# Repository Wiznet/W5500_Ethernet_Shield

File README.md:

# W5500 Ethernet Shield

## Overview

- Arduino Pin-compatible
- ARM mbed compatible operation
- Ethernet (W5500 Hardwired TCP/IP chip)

W5500 Ethernet shield is designed using the WIZnet W5500 chip. Please click the link for the further information about W5500. It supports both 3.3V & 5V. This Ethernet Shield is compatible with Arduino and ARM mbed Platform.

### Available Board List

- ARM mbed Board
	- ARM mbed Platform : ARM mbed platform Site
	- FRDM-KL25Z : Freescale
	- NXP LPC800-MAX : NXP
- Arduino Board
	- Arduino board (e.g. the Uno, Mega, Due)
	- Arduino Leonardo
- Arduino-compatible Board
	- Seeeduino v3.0 : Based on Arduino Duemilanove

## Getting Started

- [Getting Started fot Arduino](https://wizwiki.net/wiki/doku.php?id=osh:w5500_ethernet_shield_getting_started#step_2installing_the_ethernet2_library)
- [Ethernet/Ethernet2 library Reference](https://www.arduino.cc/en/Reference/Ethernet)

## Feature

- Ethernet controller W5500 of WIZnet
- SPI interface
- Internal 32Kbytes Tx/Rx buffer
- 10/100 Ethernet PHY embedded
- Hardwired TCP/IP Protocols : TCP, UDP, ICMP, IPv4, ARP, IGMP, PPPoE
- User Selectable GPIO pin
- Support SD-card slot for storage
- Support 3.3V and 5V

## Hardware Configuration
- RJ-45 with Transformer : Ethernet Port
- W5500 : a Hardwired TCP/IP Ethernet Controller
- RESET : Reset Ethernet shield and Arduino when pressed
- SD-Slot : support Micro SD card in FAT16 or FAT32 ; (Please read 'Caution' below)

## Pins usage on Arduino & ARM mbed

W5500 Ethernet shield has several configurable GPIOs

- When you operate it with other modules, you may need to change 'Chip Select' pin to a different one.
- W5500 INTn pin is linked to D2 (2,3 Short). So, if you need INTn pin. You soldering to 0R Resistor to Dx pin

**Caution)** When the user uses 5V Platform, we cannot confirm a stable operation of SD-CARD. Therefore, though 5V Platform is safe to use after going through enough tests, it is highly recommended to mount buffer & 100nF Capacitor for a secure operation.

## SPI Operation & Timing Diagram

There is a W5500 inside W5500 Ethernet shield. Therefore SPI operation & Timing Diagram of Ethernet shield follows one of W5500. For more information about W5500 chip please also refer to the chip's datasheet:

- [W5500 Wiki](https://wizwiki.net/wiki/doku.php?id=products:w5500:start)

## Dimension

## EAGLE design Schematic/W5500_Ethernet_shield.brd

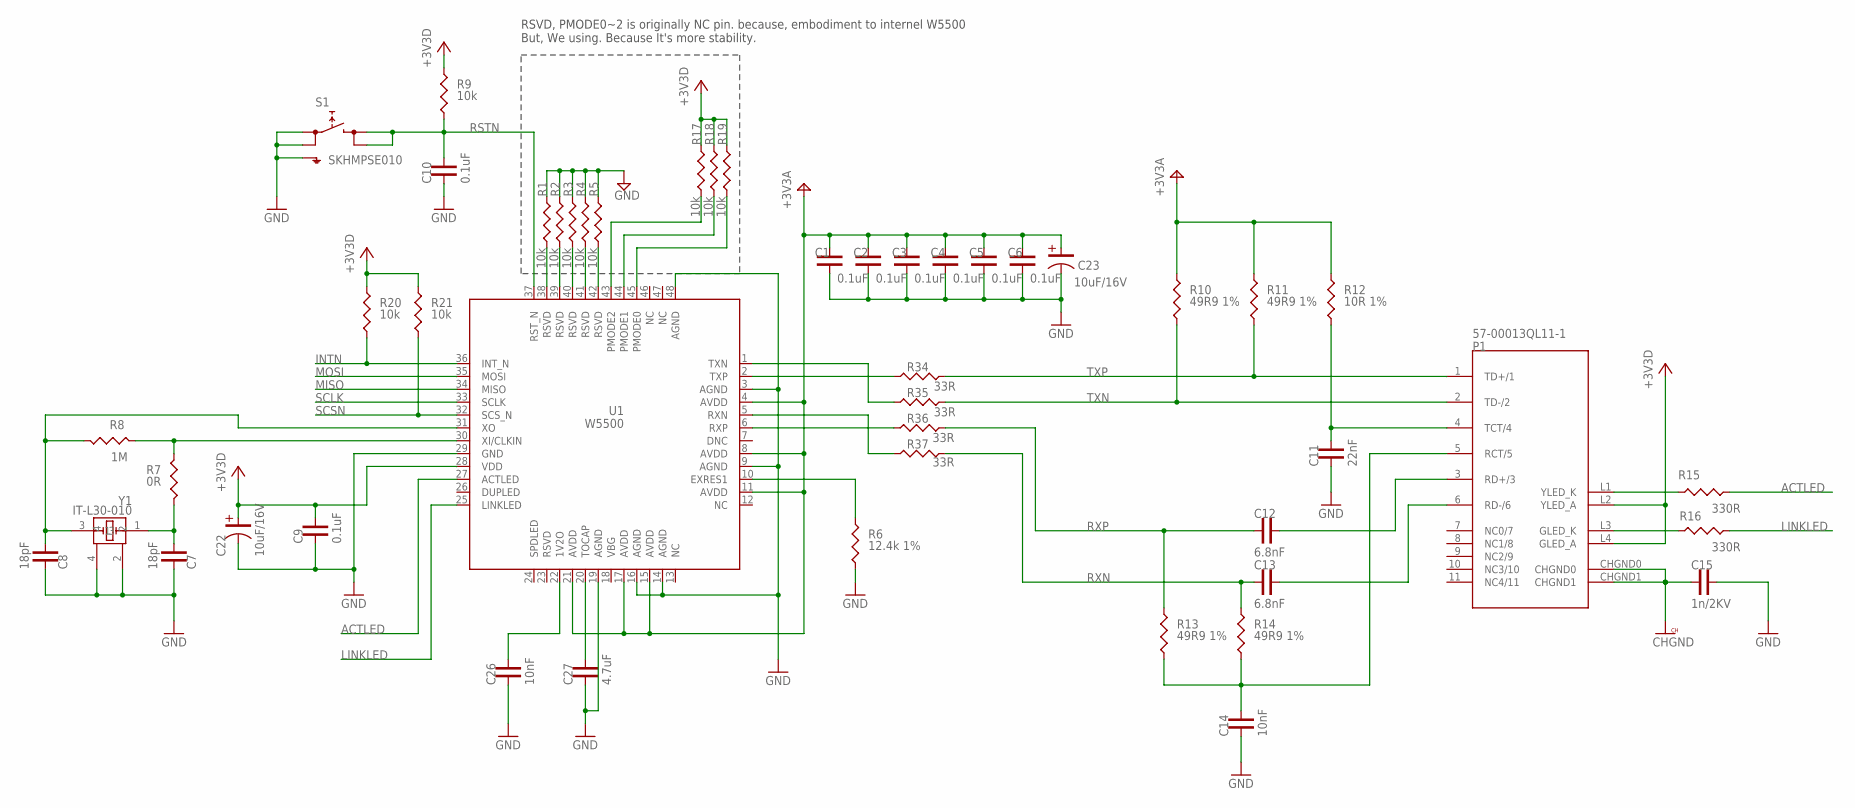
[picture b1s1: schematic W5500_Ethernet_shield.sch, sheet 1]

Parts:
C1, C2, C3, C4, C5, C6, C9, C10: 0.1uF; C-1608
C7, C8: 18pF; C-1608
C11: 22nF; C-1608
C12, C13: 6.8nF; C-1608
C14, C26: 10nF; C-1608
C15: 1n/2KV; C-1808
C22, C23: 10uF/16V; C-3216(TANTAL)
C27: 4.7uF; C-2012
P1: 57-00013QL11-1
R1, R2, R3, R4, R5, R9, R17, R18, R19, R20, R21: 10k; R-1608
R6: 12.4k 1%; R-1608
R7: 0R; R-1608
R8: 1M; R-1608
R10, R11, R13, R14: 49R9 1%; R-1608
R12: 10R 1%; R-1608
R15, R16: 330R; R-1608
R34, R35, R36, R37: 33R; R-1608
S1: SKHMPSE010; SKHMPXE010
U1: W5500
Y1: IT-L30-010

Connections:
+3V3: C9.2, C22.1, P1.L2 (YLED_A), P1.L4 (GLED_A), R9.2, R17.2, R18.2, R19.2, R20.2, R21.2, U1.28 (VDD); also elsewhere on the board
+3V3A: C1.2, C2.2, C3.2, C4.2, C5.2, C6.2, C23.1, R10.2, R11.2, R12.2, U1.4 (AVDD), U1.8 (AVDD), U1.11 (AVDD), U1.15 (AVDD), U1.17 (AVDD), U1.21 (AVDD); also elsewhere on the board
ACTLED: R15.1, U1.27 (ACTLED)
CHGND: C15.P$1, P1.CHGND0, P1.CHGND1
GND: C1.1, C2.1, C3.1, C4.1, C5.1, C6.1, C7.1, C8.1, C9.1, C10.1, C11.1, C14.1, C15.P$2, C22.2, C23.2, C26.1, C27.P$1, R1.2, R2.2, R3.2, R4.2, R5.2, R6.1, S1.1 (1.1), S1.2 (1.2), S1.5 (SH), U1.3 (AGND), U1.9 (AGND), U1.14 (AGND), U1.16 (AGND), U1.19 (AGND), U1.29 (GND), U1.48 (AGND), Y1.2, Y1.4; also elsewhere on the board
INTN: R20.1, U1.36 (INT_N); also elsewhere on the board
LINKLED: R16.1, U1.25 (LINKLED)
MISO: U1.34 (MISO); also elsewhere on the board
MOSI: U1.35 (MOSI); also elsewhere on the board
unnamed: R17.1, U1.43 (PMODE2)
unnamed: R18.1, U1.44 (PMODE1)
unnamed: R19.1, U1.45 (PMODE0)
unnamed: R1.1, U1.38 (RSVD)
unnamed: R2.1, U1.39 (RSVD)
unnamed: R3.1, U1.40 (RSVD)
unnamed: R4.1, U1.41 (RSVD)
unnamed: R5.1, U1.42 (RSVD)
unnamed: R7.2, R8.2, U1.30 (XI/CLKIN)
unnamed: C27.P$2, U1.20 (TOCAP)
unnamed: C26.2, U1.22 (1V2O)
unnamed: C12.2, P1.3 (RD+/3)
unnamed: R6.2, U1.10 (EXRES1)
unnamed: C13.2, P1.6 (RD-/6)
unnamed: C14.2, P1.5 (RCT/5), R13.1, R14.1
unnamed: R36.2, U1.6 (RXP)
unnamed: C11.2, P1.4 (TCT/4), R12.1
unnamed: C8.2, R8.1, U1.31 (XO), Y1.3
unnamed: P1.L3 (GLED_K), R16.2
unnamed: P1.L1 (YLED_K), R15.2
unnamed: R37.2, U1.5 (RXN)
unnamed: R34.2, U1.2 (TXP)
unnamed: R35.2, U1.1 (TXN)
unnamed: C7.2, R7.1, Y1.1
RSTN: C10.2, R9.1, S1.3 (2.1), S1.4 (2.2), U1.37 (RST_N); also elsewhere on the board
RXN: C13.1, R14.2, R37.1
RXP: C12.1, R13.2, R36.1
SCLK: U1.33 (SCLK); also elsewhere on the board
SCSN: R21.1, U1.32 (SCS_N); also elsewhere on the board
TXN: P1.2 (TD-/2), R10.1, R35.1
TXP: P1.1 (TD+/1), R11.1, R34.1

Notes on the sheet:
RSVD, PMODE0~2 is originally NC pin. because, embodiment to internel W5500 But, We using. Because It's more stability.

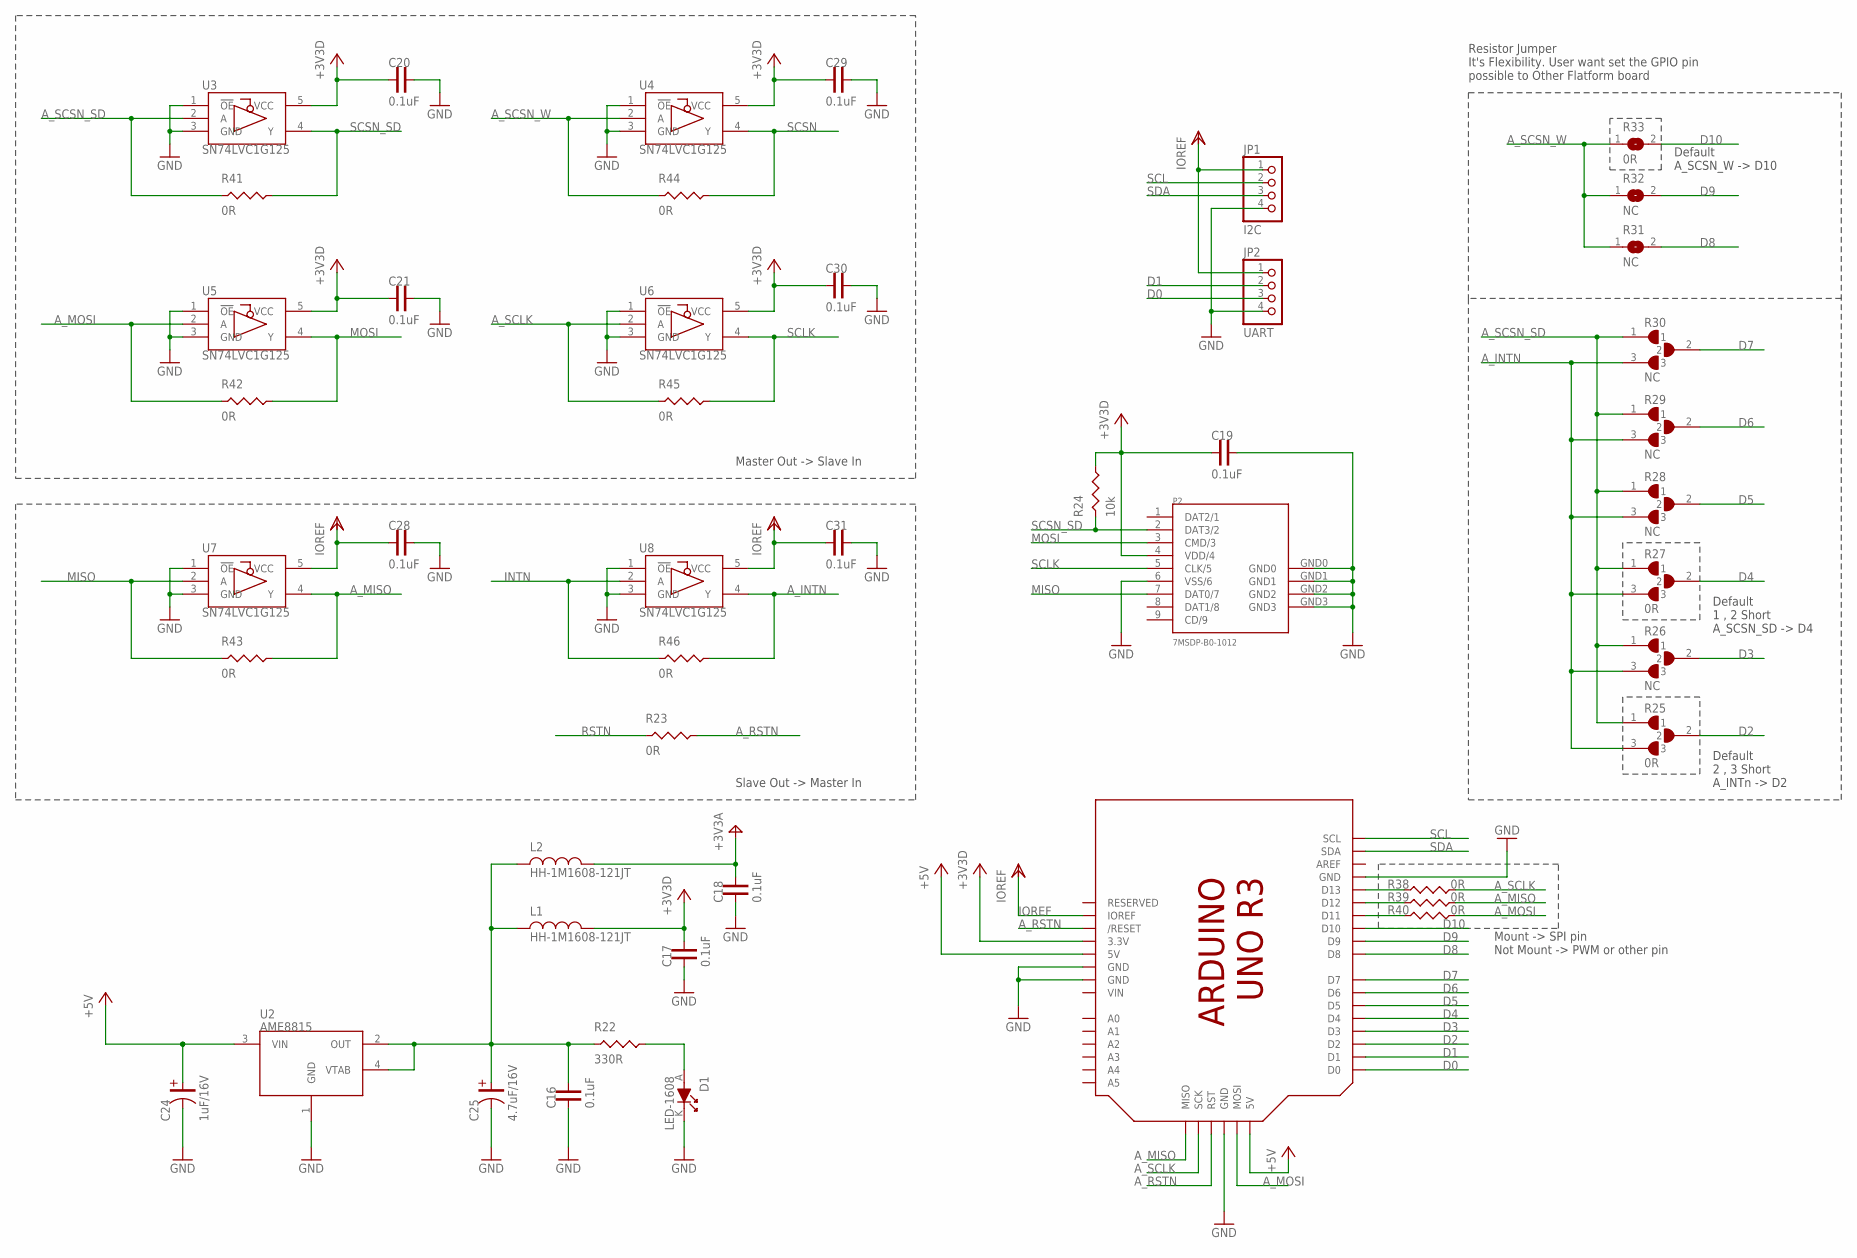
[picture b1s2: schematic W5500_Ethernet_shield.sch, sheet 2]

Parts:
C16, C17, C18, C19, C20, C21, C28, C29, C30, C31: 0.1uF; C-1608
C24: 1uF/16V; C-3216(TANTAL)
C25: 4.7uF/16V; C-3216(TANTAL)
D1: LED-1608
JP1: I2C; 1X04
JP2: UART; 1X04
L1, L2: HH-1M1608-121JT; L-1608
P2: 7MSDP-B0-1012
R22: 330R; R-1608
R23, R38, R39, R40, R41, R42, R43, R44, R45, R46: 0R; R-1608
R24: 10k; R-1608
R25, R27: 0R; RESISTOR_JUMPER_3
R26, R28, R29, R30: NC; RESISTOR_JUMPER_3
R31, R32: NC; SJW
R33: 0R; SJW
U2: AME8815
U3, U4, U5, U6, U7, U8: SN74LVC1G125
U$1: ARDUINO_R3_ICSP; ARDUINOR3_ICSP

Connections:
+3V3: C17.2, C19.1, C20.1, C21.1, C29.1, C30.1, L1.P$2 (2), P2.4 (VDD/4), R24.2, U3.5 (VCC), U4.5 (VCC), U5.5 (VCC), U6.5 (VCC), U$1.3V (3.3V); also elsewhere on the board
+3V3A: C18.2, L2.P$2 (2); also elsewhere on the board
+5V: C24.1, U2.3 (VIN), U$1.5V, U$1.5V_ICSP (5V)
A_INTN: R25.3, R26.3, R27.3, R28.3, R29.3, R30.3, R46.2, U8.4 (Y)
A_MISO: R39.2, R43.2, U7.4 (Y), U$1.MISO
A_MOSI: R40.2, R42.1, U5.2 (A), U$1.MOSI
A_RSTN: R23.2, U$1.RESET (/RESET), U$1.RESET_ICSP (RST)
A_SCLK: R38.2, R45.1, U6.2 (A), U$1.SCK
A_SCSN_SD: R25.1, R26.1, R27.1, R28.1, R29.1, R30.1, R41.1, U3.2 (A)
A_SCSN_W: R31.1, R32.1, R33.1, R44.1, U4.2 (A)
D0: JP2.3, U$1.D0
D1: JP2.2, U$1.D1
D2: R25.2, U$1.D2
D3: R26.2, U$1.D3
D4: R27.2, U$1.D4
D5: R28.2, U$1.D5
D6: R29.2, U$1.D6
D7: R30.2, U$1.D7
D8: R31.2, U$1.D8
D9: R32.2, U$1.D9
D10: R33.2, U$1.D10
GND: C16.1, C17.1, C18.1, C19.2, C20.2, C21.2, C24.2, C25.2, C28.2, C29.2, C30.2, C31.2, D1.K, JP1.4, JP2.4, P2.6 (VSS/6), P2.GND0, P2.GND1, P2.GND2, P2.GND3, U2.1 (GND), U3.1 (!OE), U3.3 (GND), U4.1 (!OE), U4.3 (GND), U5.1 (!OE), U5.3 (GND), U6.1 (!OE), U6.3 (GND), U7.1 (!OE), U7.3 (GND), U8.1 (!OE), U8.3 (GND), U$1.GND, U$1.GND@1 (GND), U$1.GND@2 (GND), U$1.GND@3 (GND); also elsewhere on the board
INTN: R46.1, U8.2 (A); also elsewhere on the board
IOREF: C28.1, C31.1, JP1.1, JP2.1, U7.5 (VCC), U8.5 (VCC), U$1.IOREF
MISO: P2.7 (DAT0/7), R43.1, U7.2 (A); also elsewhere on the board
MOSI: P2.3 (CMD/3), R42.2, U5.4 (Y); also elsewhere on the board
unnamed: D1.A, R22.2
unnamed: R38.1, U$1.D13
unnamed: C16.2, C25.1, L1.1, L2.1, R22.1, U2.2 (OUT), U2.4 (VTAB)
unnamed: R39.1, U$1.D12
unnamed: R40.1, U$1.D11
RSTN: R23.1; also elsewhere on the board
SCL: JP1.2, U$1.SCL
SCLK: P2.5 (CLK/5), R45.2, U6.4 (Y); also elsewhere on the board
SCSN: R44.2, U4.4 (Y); also elsewhere on the board
SCSN_SD: P2.2 (DAT3/2), R24.1, R41.2, U3.4 (Y)
SDA: JP1.3, U$1.SDA

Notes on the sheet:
Master Out -> Slave In
Slave Out -> Master In
Resistor Jumper It's Flexibility. User want set the GPIO pin possible to Other Flatform board
Default 2 , 3 Short A_INTn -> D2
Default 1 , 2 Short A_SCSN_SD -> D4
Default A_SCSN_W -> D10
Mount -> SPI pin Not Mount -> PWM or other pin

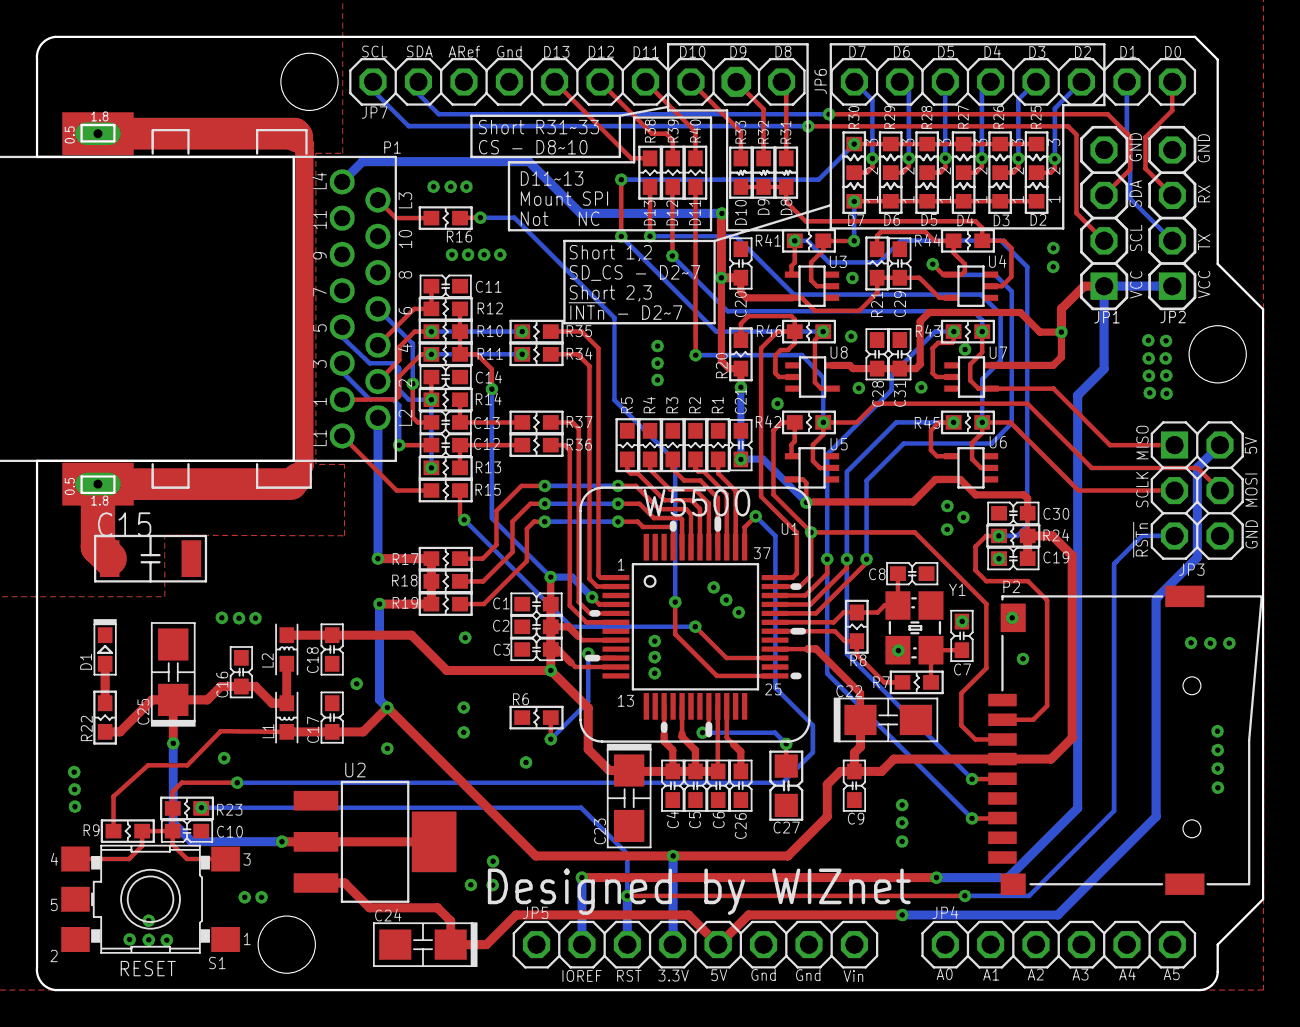
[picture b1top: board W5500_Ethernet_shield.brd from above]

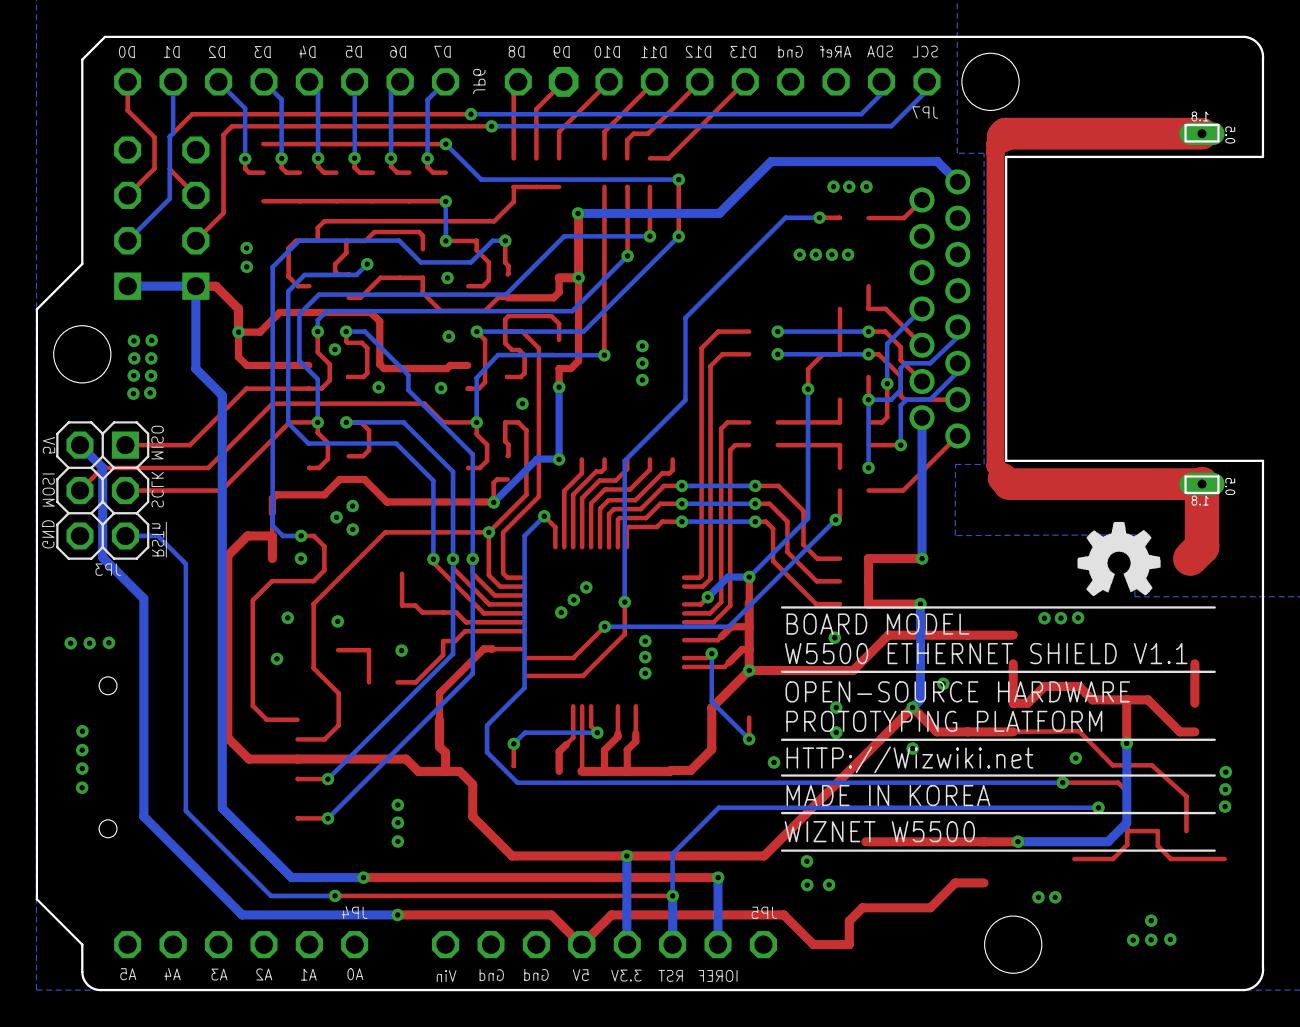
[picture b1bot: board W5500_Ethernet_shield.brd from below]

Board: 2 copper layers, 68.6 x 53.3 mm, 97 parts (2 on the bottom side), 68 nets.

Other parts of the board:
U$4: OSHP-LOGO
U$7: IOPIOT_LOGO_3

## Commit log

2018-02-28 Initial Release
2018-02-28 added gerber files
    Added W5500 Ethernet shield V1.0 gerber file
2018-02-28 Update to Rev1.1 files
    In Rev 1.0, GND pin of “RESET” button(S1) was floating.
    This change in Rev1.1 will solve the floating problem. (Connect to GND
    with adding VIA.)
    Refer to below picture.
    GND is reinforced by adding via hole to whole board
    Via located was close to D11 pattern(R20). so that via is separated.
